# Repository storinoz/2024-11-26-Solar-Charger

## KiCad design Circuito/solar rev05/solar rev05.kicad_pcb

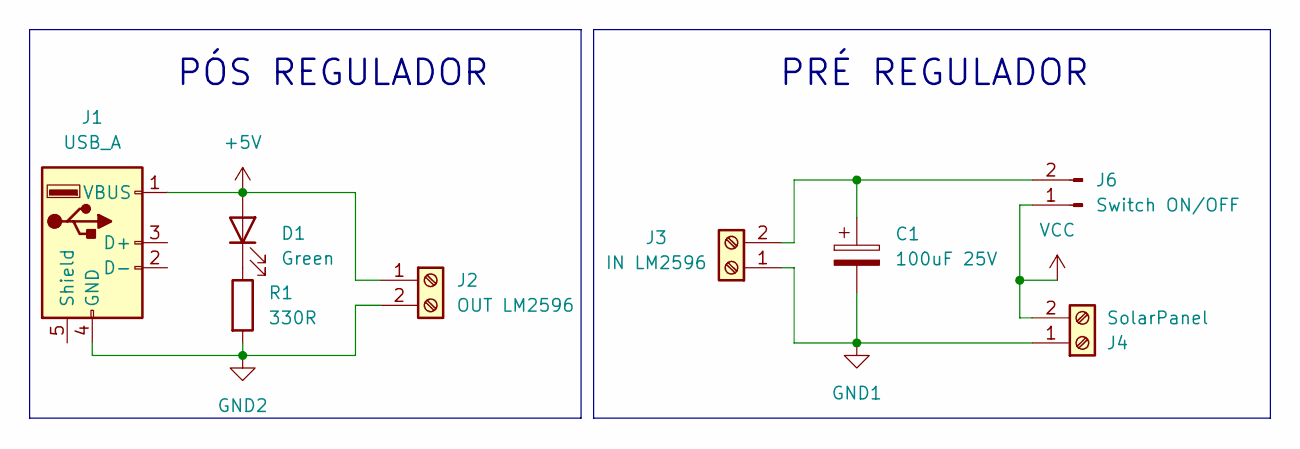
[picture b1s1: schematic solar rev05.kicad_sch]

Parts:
C1: 100uF 25V; CP_Radial_D8.0mm_P5.00mm
D1: Green; LED_D5.0mm
J1: USB_A; USB_A_Molex_67643_Horizontal
J2: OUT LM2596; TerminalBlock_bornier-2_P5.08mm
J3: IN LM2596; TerminalBlock_bornier-2_P5.08mm
J4: SolarPanel; TerminalBlock_bornier-2_P5.08mm
J6: Switch ON/OFF; PinSocket_2x01_P2.54mm_Vertical
R1: 330R; R_Axial_DIN0414_L11.9mm_D4.5mm_P15.24mm_Horizontal

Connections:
+5V: D1.2 (A), J1.1 (VBUS), J2.1
GND1: C1.2, J3.1, J4.1
GND2: J1.4 (GND), J2.2, R1.2
unnamed: D1.1 (K), R1.1
unnamed: C1.1, J3.2, J6.2
VCC: J4.2, J6.1

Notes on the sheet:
PRÉ REGULADOR
PÓS REGULADOR

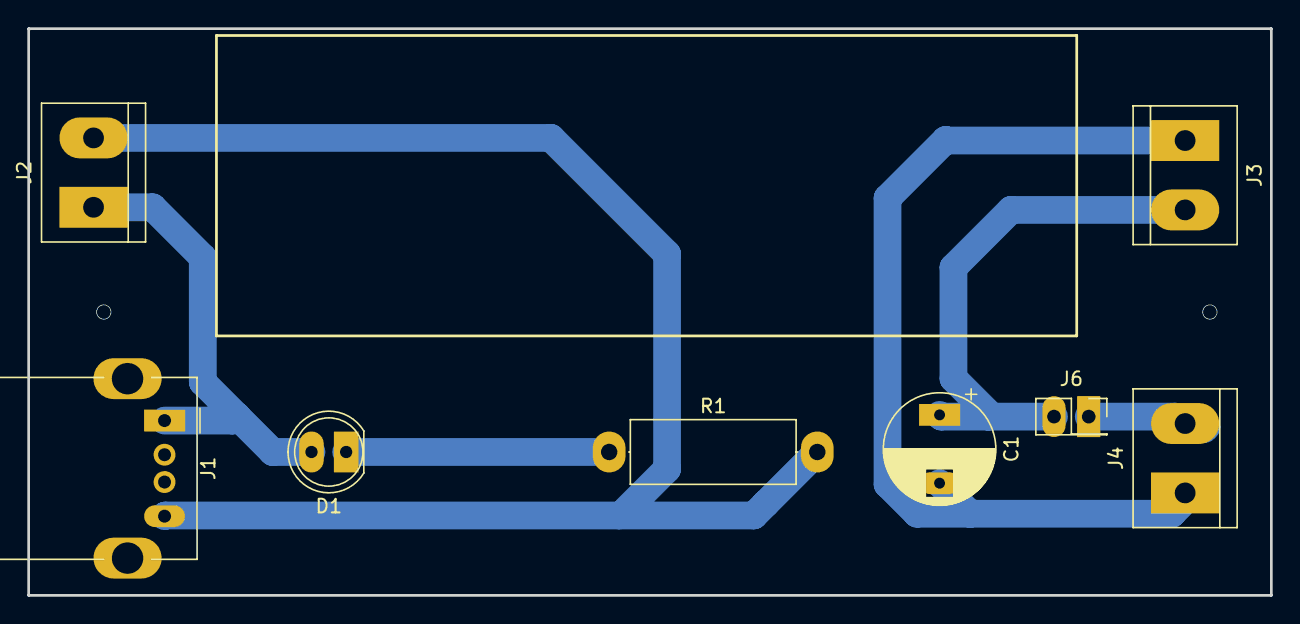
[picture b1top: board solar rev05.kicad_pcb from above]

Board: 2 copper layers, 91.0 x 41.5 mm, 8 parts (0 on the bottom side), 6 nets.
